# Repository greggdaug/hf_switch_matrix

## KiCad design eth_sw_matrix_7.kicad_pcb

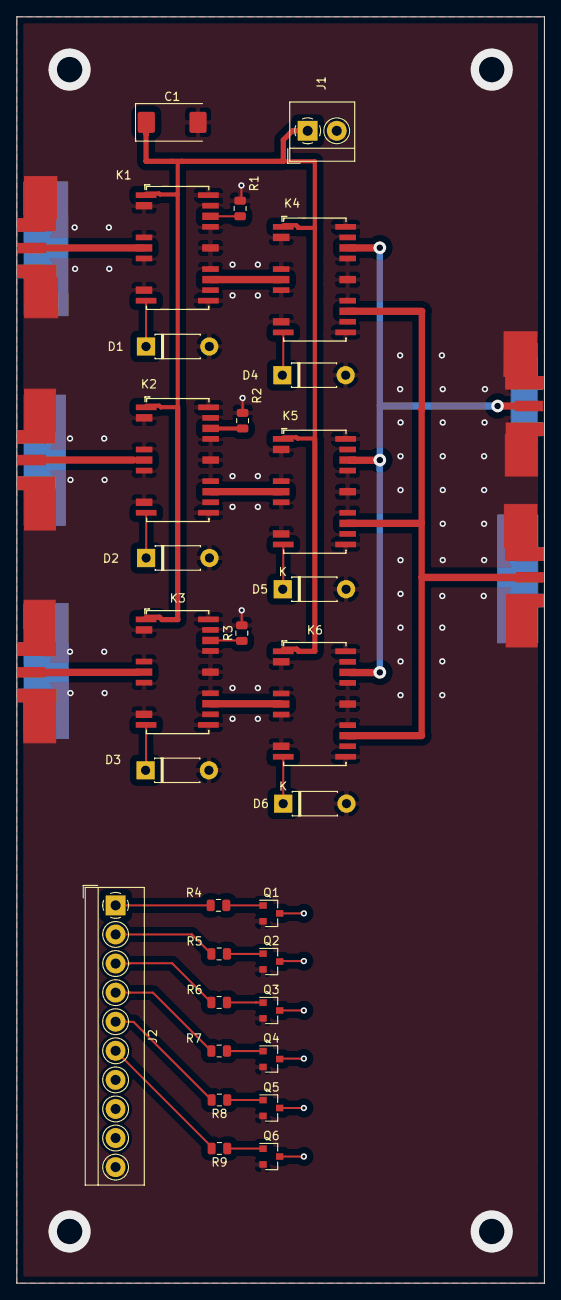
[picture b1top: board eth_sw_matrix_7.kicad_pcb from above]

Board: 4 copper layers, 63.5 x 152.4 mm, 35 parts (0 on the bottom side), 31 nets.

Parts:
C1: CP1; CP_EIA-7343-30_AVX-N
D1, D2, D3, D4, D5, D6: SM4001; D_DO-41_SOD81_P7.62mm_Horizontal
J1: Screw_Terminal_01x02; TerminalBlock_4Ucon_1x02_P3.50mm_Horizontal
J2: Screw_Terminal_01x10; TerminalBlock_4Ucon_1x10_P3.50mm_Horizontal
J3, J4, J5, J6, J7: Conn_Coaxial; conn_sma_edgemnt
K1, K2, K3, K4, K5, K6: HF3-57; Relay_SPDT_AXICOM_HF3Series_50ohms_Pitch1.27mm
Q1, Q2, Q3, Q4, Q5, Q6: MMBT3904; SOT-23
R1, R2, R3: 50; R_0805_2012Metric
R4, R5, R6, R7, R8, R9: 10k; R_0805_2012Metric

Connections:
+12V: C1.1, J1.1, K1.1, K2.1, K3.1, K4.1, K5.1, K6.1
/cntl1: D1.1, K1.11, Q1.3
/cntl2: D2.1, K2.11, Q2.3
/cntl3: D3.1, K3.11, Q3.3
/cntl4: D4.1, K4.11, Q4.3
/cntl5: D5.1, K5.11, Q5.3
/cntl6: D6.1, K6.11, Q6.3
GND: C1.2, D1.2, D2.2, D3.2, D4.2, D5.2, D6.2, J1.2, J2.10, J3.2, J4.2, J5.2, J6.2, J7.2, K1.2, K1.5, K1.7, K1.10, K1.12, K1.13, K1.15, K1.17, K1.19, K1.21, K1.22, K2.2, K2.5, K2.7, K2.10, K2.12, K2.13, K2.15, K2.17, K2.19, K2.21, K2.22, K3.2, K3.5, K3.7, K3.10, K3.12, K3.13, K3.15, K3.17, K3.19, K3.21, K3.22, K4.2, K4.5, K4.7, K4.10, K4.12, K4.13, K4.15, K4.17, K4.19, K4.21, K4.22, K5.2, K5.5, K5.7, K5.10, K5.12, K5.13, K5.15, K5.17, K5.19, K5.21, K5.22, K6.2, K6.5, K6.7, K6.10, K6.12, K6.13, K6.15, K6.17, K6.19, K6.21, K6.22, Q1.2, Q2.2, Q3.2, Q4.2, Q5.2, Q6.2, R1.2, R2.2, R3.2
unnamed: J2.1, R4.2
unnamed: J2.2, R5.2
unnamed: J2.3, R6.2
unnamed: J2.4, R7.2
unnamed: J2.5, R8.2
unnamed: J2.6, R9.2
unnamed: J3.1, K1.6
unnamed: J4.1, K2.6
unnamed: J5.1, K3.6
unnamed: J6.1, K4.14, K5.14, K6.14
unnamed: J7.1, K4.20, K5.20, K6.20
unnamed: K1.14, K4.6
unnamed: K1.20, R1.1
unnamed: K2.14, K5.6
unnamed: K2.20, R2.1
unnamed: K3.14, K6.6
unnamed: K3.20, R3.1
unnamed: Q1.1, R4.1
unnamed: Q2.1, R5.1
unnamed: Q3.1, R6.1
unnamed: Q4.1, R7.1
unnamed: Q5.1, R8.1
unnamed: Q6.1, R9.1

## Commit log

2022-03-02 3:2 HF Switch Matrix
    100W 3:2 HF Switch Matrix design files
2022-04-10 control updates
